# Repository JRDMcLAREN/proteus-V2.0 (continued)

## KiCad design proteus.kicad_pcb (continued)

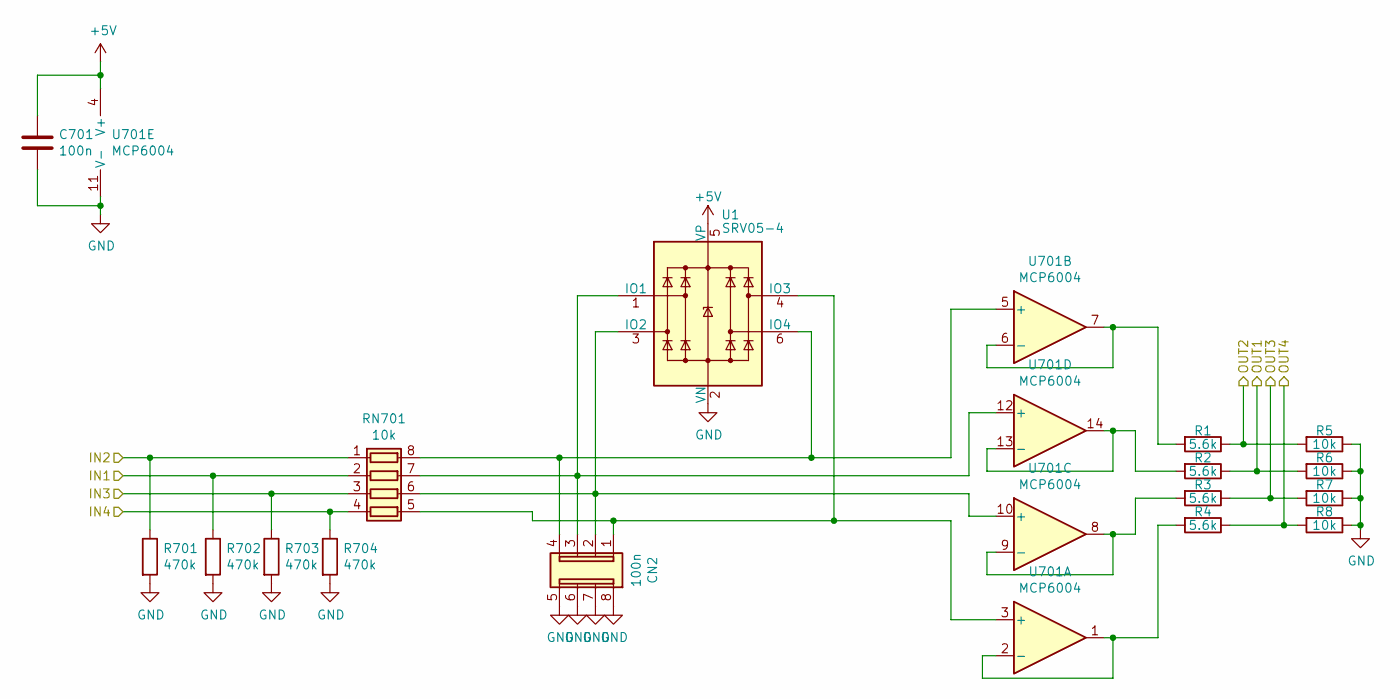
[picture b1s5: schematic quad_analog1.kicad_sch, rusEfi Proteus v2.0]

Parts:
C701: 100n; C_0603_1608Metric; LCSC C14663
CN2: 100n; R_Array_Convex_4x0603; LCSC C29718
R1, R2, R3, R4: 5.6k; R_0603_1608Metric; LCSC C25908
R5, R6, R7, R8: 10k; R_0603_1608Metric; LCSC C25744
R701, R702, R703, R704: 470k; R_0603_1608Metric; LCSC C25790
RN701: 10k; R_Array_Convex_4x0603; LCSC C29718
U1: SRV05-4; SOT-23-6; LCSC C85364
U701: MCP6004; TSSOP-14_4.4x5mm_P0.65mm; LCSC C50282

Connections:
+5V: C701.1, U1.5 (VP), U701.4 (V+); also elsewhere on the board
/AV1: R702.1, RN701.2 (R2.1); also elsewhere on the board
/AV2: R701.1, RN701.1 (R1.1); also elsewhere on the board
/AV3: R703.1, RN701.3 (R3.1); also elsewhere on the board
/AV4: R704.1, RN701.4 (R4.1); also elsewhere on the board
/mcu/AV1: R2.1, R6.2; also elsewhere on the board
/mcu/AV2: R1.1, R5.2; also elsewhere on the board
/mcu/AV3: R3.1, R7.2; also elsewhere on the board
/mcu/AV4: R4.1, R8.2; also elsewhere on the board
GND: C701.2, CN2.5 (R4.2), CN2.6 (R3.2), CN2.7 (R2.2), CN2.8 (R1.2), R5.1, R6.1, R7.1, R8.1, R701.2, R702.2, R703.2, R704.2, U1.2 (VN), U701.11 (V-); also elsewhere on the board
unnamed: CN2.1 (R1.1), RN701.5 (R4.2), U1.4 (IO3), U701.3 (+)
unnamed: CN2.2 (R2.1), RN701.6 (R3.2), U1.3 (IO2), U701.10 (+)
unnamed: CN2.3 (R3.1), RN701.7 (R2.2), U1.1 (IO1), U701.12 (+)
unnamed: CN2.4 (R4.1), RN701.8 (R1.2), U1.6 (IO4), U701.5 (+)
unnamed: R4.2, U701.1, U701.2 (-)
unnamed: R1.2, U701.6 (-), U701.7
unnamed: R3.2, U701.8, U701.9 (-)
unnamed: R2.2, U701.13 (-), U701.14

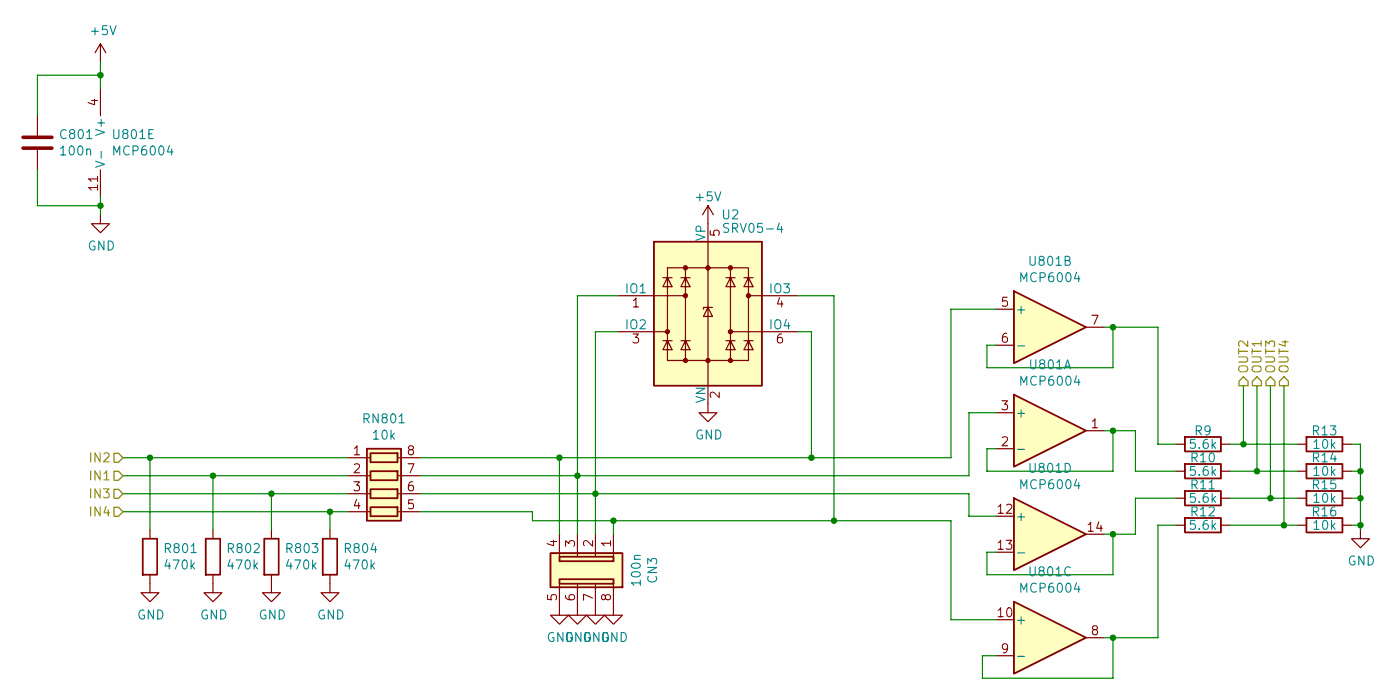
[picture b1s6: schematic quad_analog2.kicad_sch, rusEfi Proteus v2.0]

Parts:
C801: 100n; C_0603_1608Metric; LCSC C14663
CN3: 100n; R_Array_Convex_4x0603; LCSC C29718
R9, R10, R11, R12: 5.6k; R_0603_1608Metric; LCSC C25908
R13, R14, R15, R16: 10k; R_0603_1608Metric; LCSC C25744
R801, R802, R803, R804: 470k; R_0603_1608Metric; LCSC C25790
RN801: 10k; R_Array_Convex_4x0603; LCSC C29718
U2: SRV05-4; SOT-23-6; LCSC C85364
U801: MCP6004; TSSOP-14_4.4x5mm_P0.65mm; LCSC C50282

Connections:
+5V: C801.1, U2.5 (VP), U801.4 (V+); also elsewhere on the board
/AV5: R802.1, RN801.2 (R2.1); also elsewhere on the board
/AV6: R801.1, RN801.1 (R1.1); also elsewhere on the board
/AV7: R803.1, RN801.3 (R3.1); also elsewhere on the board
/AV8: R804.1, RN801.4 (R4.1); also elsewhere on the board
/mcu/AV5: R10.1, R14.2; also elsewhere on the board
/mcu/AV6: R9.1, R13.2; also elsewhere on the board
/mcu/AV7: R11.1, R15.2; also elsewhere on the board
/mcu/AV8: R12.1, R16.2; also elsewhere on the board
GND: C801.2, CN3.5 (R4.2), CN3.6 (R3.2), CN3.7 (R2.2), CN3.8 (R1.2), R13.1, R14.1, R15.1, R16.1, R801.2, R802.2, R803.2, R804.2, U2.2 (VN), U801.11 (V-); also elsewhere on the board
unnamed: CN3.1 (R1.1), RN801.5 (R4.2), U2.4 (IO3), U801.10 (+)
unnamed: CN3.2 (R2.1), RN801.6 (R3.2), U2.3 (IO2), U801.12 (+)
unnamed: CN3.3 (R3.1), RN801.7 (R2.2), U2.1 (IO1), U801.3 (+)
unnamed: CN3.4 (R4.1), RN801.8 (R1.2), U2.6 (IO4), U801.5 (+)
unnamed: R10.2, U801.1, U801.2 (-)
unnamed: R9.2, U801.6 (-), U801.7
unnamed: R12.2, U801.8, U801.9 (-)
unnamed: R11.2, U801.13 (-), U801.14

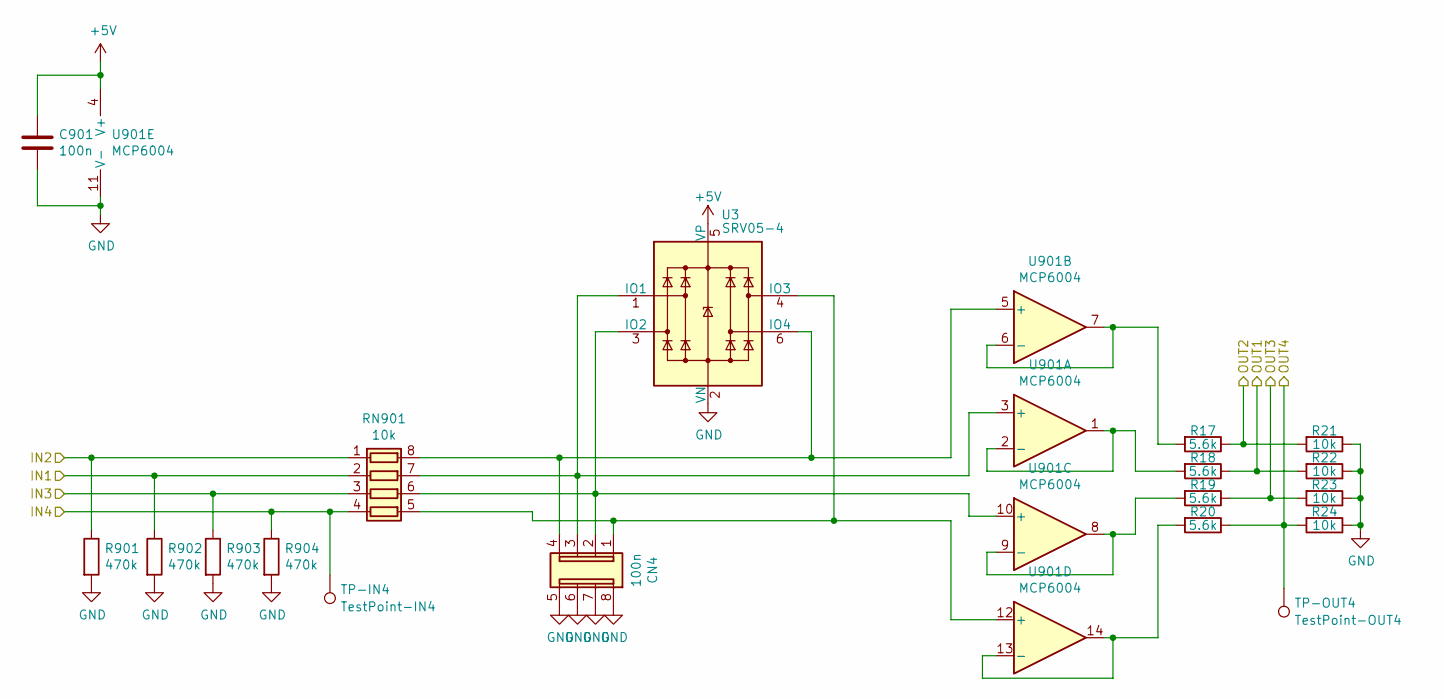
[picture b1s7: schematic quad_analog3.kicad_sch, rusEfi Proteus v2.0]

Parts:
C901: 100n; C_0603_1608Metric; LCSC C14663
CN4: 100n; R_Array_Convex_4x0603; LCSC C29718
R17, R18, R19, R20: 5.6k; R_0603_1608Metric; LCSC C25908
R21, R22, R23, R24: 10k; R_0603_1608Metric; LCSC C25744
R901, R902, R903, R904: 470k; R_0603_1608Metric; LCSC C25790
RN901: 10k; R_Array_Convex_4x0603; LCSC C29718
TP-IN4: TestPoint-IN4; TestPoint_Pad_D1.0mm
TP-OUT4: TestPoint-OUT4; TestPoint_Pad_D1.0mm
U3: SRV05-4; SOT-23-6; LCSC C85364
U901: MCP6004; TSSOP-14_4.4x5mm_P0.65mm; LCSC C50282

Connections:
+5V: C901.1, U3.5 (VP), U901.4 (V+); also elsewhere on the board
/AV9: R902.1, RN901.2 (R2.1); also elsewhere on the board
/AV10: R901.1, RN901.1 (R1.1); also elsewhere on the board
/AV11: R903.1, RN901.3 (R3.1); also elsewhere on the board
/mcu/AV9: R18.1, R22.2; also elsewhere on the board
/mcu/AV10: R17.1, R21.2; also elsewhere on the board
/mcu/AV11: R19.1, R23.2; also elsewhere on the board
/quad_analog3/IN4: R904.1, RN901.4 (R4.1), TP-IN4.1
/quad_analog3/OUT4: R20.1, R24.2, TP-OUT4.1
GND: C901.2, CN4.5 (R4.2), CN4.6 (R3.2), CN4.7 (R2.2), CN4.8 (R1.2), R21.1, R22.1, R23.1, R24.1, R901.2, R902.2, R903.2, R904.2, U3.2 (VN), U901.11 (V-); also elsewhere on the board
unnamed: CN4.1 (R1.1), RN901.5 (R4.2), U3.4 (IO3), U901.12 (+)
unnamed: CN4.2 (R2.1), RN901.6 (R3.2), U3.3 (IO2), U901.10 (+)
unnamed: CN4.3 (R3.1), RN901.7 (R2.2), U3.1 (IO1), U901.3 (+)
unnamed: CN4.4 (R4.1), RN901.8 (R1.2), U3.6 (IO4), U901.5 (+)
unnamed: R18.2, U901.1, U901.2 (-)
unnamed: R17.2, U901.6 (-), U901.7
unnamed: R19.2, U901.8, U901.9 (-)
unnamed: R20.2, U901.13 (-), U901.14

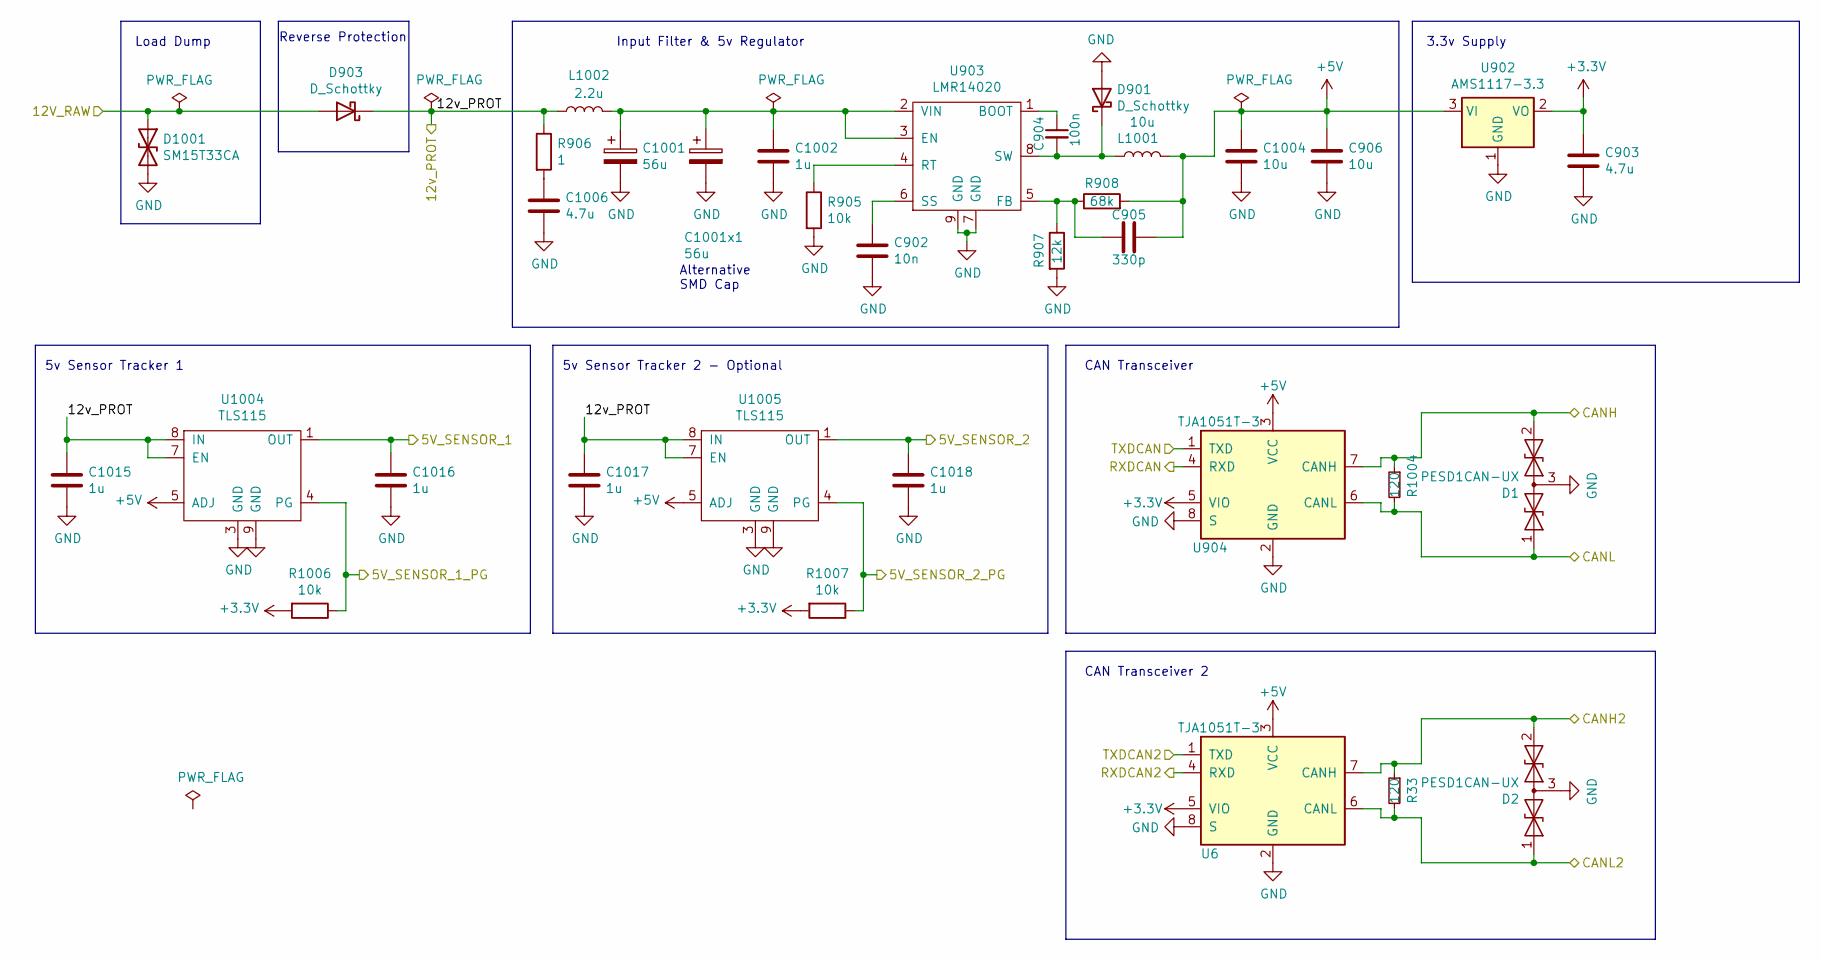
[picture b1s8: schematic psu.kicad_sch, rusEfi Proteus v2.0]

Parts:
C902: 10n; C_0603_1608Metric; LCSC C57112
C903, C1006: 4.7u; C_0603_1608Metric; LCSC C19666
C904: 100n; C_0603_1608Metric; LCSC C14663
C905: 330p; C_0603_1608Metric; LCSC C13533
C906, C1004: 10u; C_1206_3216Metric; LCSC C13585
C1001: 56u; CP_Radial_D8.0mm_P3.50mm; LCSC N/A
C1001x1: 56u; CP_Elec_6.3x9.9; LCSC N/A
C1002, C1015, C1016, C1017, C1018: 1u; C_0603_1608Metric; LCSC C15849
D1, D2: PESD1CAN-UX; SOT-323_SC-70; LCSC C152727
D901, D903: D_Schottky; D_SMA; LCSC C8678
D1001: SM15T33CA; D_SMC; LCSC C151281
L1001: 10u; MWSA0503; LCSC C408412
L1002: 2.2u; L_1210_3225Metric; LCSC C36828
R33, R1004: 120; R_0603_1608Metric; LCSC C22787
R905, R1006, R1007: 10k; R_0603_1608Metric; LCSC C25744
R906: 1; R_0603_1608Metric; LCSC C25086
R907: 12k; R_0603_1608Metric; LCSC C25752
R908: 68k; R_0603_1608Metric; LCSC C36871
U6, U904: TJA1051T-3; SOIC-8_3.9x4.9mm_P1.27mm; LCSC C38695
U902: AMS1117-3.3; SOT-223-3_TabPin2; LCSC C6186
U903: LMR14020; SOIC-8-1EP_3.9x4.9mm_P1.27mm_EP2.29x3mm; LCSC C187824
U1004, U1005: TLS115; Infineon_PG-DSO-8-43; LCSC N/A

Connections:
+3V3: C903.1, R1006.2, R1007.2, U6.5 (VIO), U902.2 (VO), U904.5 (VIO); also elsewhere on the board
+5V: C905.1, C906.1, C1004.1, L1001.2, R908.2, U6.3 (VCC), U902.3 (VI), U904.3 (VCC), U1004.5 (ADJ), U1005.5 (ADJ); also elsewhere on the board
/5V_SENSOR_1: C1016.1, U1004.1 (OUT); also elsewhere on the board
/5V_SENSOR_2: C1018.1, U1005.1 (OUT); also elsewhere on the board
/12V_PROT: C1015.1, C1017.1, D903.1 (K), L1002.1, R906.1, U1004.7 (EN), U1004.8 (IN), U1005.7 (EN), U1005.8 (IN); also elsewhere on the board
/12V_RAW: D903.2 (A), D1001.1 (A1); also elsewhere on the board
/CAN2+: D2.2 (A2), R33.1, U6.7 (CANH); also elsewhere on the board
/CAN2-: D2.1 (A1), R33.2, U6.6 (CANL); also elsewhere on the board
/CAN+: D1.2 (A2), R1004.1, U904.7 (CANH); also elsewhere on the board
/CAN-: D1.1 (A1), R1004.2, U904.6 (CANL); also elsewhere on the board
/mcu/5V_SENSOR_1_PG: R1006.1, U1004.4 (PG); also elsewhere on the board
/mcu/5V_SENSOR_2_PG: R1007.1, U1005.4 (PG); also elsewhere on the board
/mcu/CAN2_RX: U6.4 (RXD); also elsewhere on the board
/mcu/CAN2_TX: U6.1 (TXD); also elsewhere on the board
/mcu/CAN_RX: U904.4 (RXD); also elsewhere on the board
/mcu/CAN_TX: U904.1 (TXD); also elsewhere on the board
GND: C902.2, C903.2, C906.2, C1001.2, C1001x1.2, C1002.2, C1004.2, C1006.2, C1015.2, C1016.2, C1017.2, C1018.2, D1.3 (common), D2.3 (common), D901.2 (A), D1001.2 (A2), R905.2, R907.2, U6.2 (GND), U6.8 (S), U902.1 (GND), U903.7 (GND), U903.9 (GND), U904.2 (GND), U904.8 (S), U1004.3 (GND), U1004.9 (GND), U1005.3 (GND), U1005.9 (GND); also elsewhere on the board
unnamed: C1006.1, R906.2
unnamed: C904.2, D901.1 (K), L1001.1, U903.8 (SW)
unnamed: C904.1, U903.1 (BOOT)
unnamed: C1001.1, C1001x1.1, C1002.1, L1002.2, U903.2 (VIN), U903.3 (EN)
unnamed: C905.2, R907.1, R908.1, U903.5 (FB)
unnamed: R905.1, U903.4 (RT)
unnamed: C902.1, U903.6 (SS)

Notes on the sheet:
Alternative SMD Cap
3.3v Supply
CAN Transceiver 2
5v Sensor Tracker 2 - Optional
Input Filter & 5v Regulator
CAN Transceiver
Reverse Protection
Load Dump
5v Sensor Tracker 1

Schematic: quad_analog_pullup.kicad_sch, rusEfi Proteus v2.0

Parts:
C1101, C1409: 100n; C_0603_1608Metric; LCSC C14663
CN1: 100n; R_Array_Convex_4x0603; LCSC C29718
R25, R26, R27, R28: 5.6k; R_0603_1608Metric; LCSC C25908
R29, R30, R31, R32: 10k; R_0603_1608Metric; LCSC C25744
R1101, R1102, R1103, R1104: 2.7k; R_0603_1608Metric; LCSC C13167
RN1101: 10k; R_Array_Convex_4x0603; LCSC C29718
U4: SRV05-4; SOT-23-6; LCSC C85364
U1101: MCP6004; TSSOP-14_4.4x5mm_P0.65mm; LCSC C50282

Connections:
+5V: C1101.1, U4.5 (VP), U1101.4 (V+); also elsewhere on the board
/5V_SENSOR_1: C1409.2, R1101.1, R1102.1, R1103.1, R1104.1; also elsewhere on the board
/AT1: R1102.2, RN1101.2 (R2.1); also elsewhere on the board
/AT2: R1101.2, RN1101.1 (R1.1); also elsewhere on the board
/AT3: R1104.2, RN1101.4 (R4.1); also elsewhere on the board
/AT4: R1103.2, RN1101.3 (R3.1); also elsewhere on the board
/mcu/AT1: R26.1, R30.2; also elsewhere on the board
/mcu/AT2: R25.1, R29.2; also elsewhere on the board
/mcu/AT3: R28.1, R32.2; also elsewhere on the board
/mcu/AT4: R27.1, R31.2; also elsewhere on the board
GND: C1101.2, C1409.1, CN1.5 (R4.2), CN1.6 (R3.2), CN1.7 (R2.2), CN1.8 (R1.2), R29.1, R30.1, R31.1, R32.1, U4.2 (VN), U1101.11 (V-); also elsewhere on the board
unnamed: CN1.1 (R1.1), RN1101.5 (R4.2), U4.4 (IO3), U1101.12 (+)
unnamed: CN1.2 (R2.1), RN1101.6 (R3.2), U4.3 (IO2), U1101.10 (+)
unnamed: CN1.3 (R3.1), RN1101.7 (R2.2), U4.1 (IO1), U1101.3 (+)
unnamed: CN1.4 (R4.1), RN1101.8 (R1.2), U4.6 (IO4), U1101.5 (+)
unnamed: R26.2, U1101.1, U1101.2 (-)
unnamed: R25.2, U1101.6 (-), U1101.7
unnamed: R27.2, U1101.8, U1101.9 (-)
unnamed: R28.2, U1101.13 (-), U1101.14

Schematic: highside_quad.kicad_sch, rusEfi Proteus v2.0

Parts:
C1301, C1302, C1303, C1304: 10n; C_0603_1608Metric; LCSC C57112
R34, R35, R36, R37: 4.7k; R_0805_2012Metric; LCSC C17673
R1105, R1107, R1109, R1111: 10k; R_0603_1608Metric; LCSC C25744
R1106, R1108, R1110, R1112: 120; R_0603_1608Metric; LCSC C22787
RN1301: 10k; R_Array_Convex_4x0603; LCSC C29718
U1102, U1103, U1104, U1105: BTS4175SGA; SOIC-8_3.9x4.9mm_P1.27mm; LCSC C152451

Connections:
+3V3: R1105.2, R1107.2, R1109.2, R1111.2; also elsewhere on the board
/12V_MR: U1102.5 (VS), U1102.6 (VS), U1102.7 (VS), U1102.8 (VS), U1103.5 (VS), U1103.6 (VS), U1103.7 (VS), U1103.8 (VS), U1104.5 (VS), U1104.6 (VS), U1104.7 (VS), U1104.8 (VS), U1105.5 (VS), U1105.6 (VS), U1105.7 (VS), U1105.8 (VS); also elsewhere on the board
/HS1: C1301.1, R34.1, U1102.3 (OUT); also elsewhere on the board
/HS2: C1302.1, R35.1, U1103.3 (OUT); also elsewhere on the board
/HS3: C1303.1, R36.1, U1104.3 (OUT); also elsewhere on the board
/HS4: C1304.1, R37.1, U1105.3 (OUT); also elsewhere on the board
/highside_quad/IN1: RN1301.1 (R1.1); also elsewhere on the board
/highside_quad/IN2: RN1301.2 (R2.1); also elsewhere on the board
/highside_quad/IN3: RN1301.3 (R3.1); also elsewhere on the board
/highside_quad/IN4: RN1301.4 (R4.1); also elsewhere on the board
GND: C1301.2, C1302.2, C1303.2, C1304.2, R34.2, R35.2, R36.2, R37.2, R1106.2, R1108.2, R1110.2, R1112.2; also elsewhere on the board
unnamed: RN1301.8 (R1.2), U1102.2 (IN)
unnamed: RN1301.7 (R2.2), U1103.2 (IN)
unnamed: RN1301.6 (R3.2), U1104.2 (IN)
unnamed: RN1301.5 (R4.2), U1105.2 (IN)
unnamed: R1106.1, U1102.1 (GND)
unnamed: R1105.1, U1102.4 (ST)
unnamed: R1108.1, U1103.1 (GND)
unnamed: R1107.1, U1103.4 (ST)
unnamed: R1110.1, U1104.1 (GND)
unnamed: R1109.1, U1104.4 (ST)
unnamed: R1112.1, U1105.1 (GND)
unnamed: R1111.1, U1105.4 (ST)

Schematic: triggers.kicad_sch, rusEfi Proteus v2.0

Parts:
C1204, C1205, C1207, C1208, C1209, C1210, C1401, C1402, C1403, C1404, C1405, C1406, C1407, C1408: 1n; C_0603_1608Metric; LCSC C1588
C1211: 100n; C_0603_1608Metric; LCSC C14663
C1212: 1u; C_0603_1608Metric; LCSC C15849
JP1201: Jumper_3_Bridged12; SolderJumper-3_P1.3mm_Bridged12_RoundedPad1.0x1.5mm; LCSC N/A
R1201, R1202, R1203, R1204, R1401, R1402, R1403, R1404, R1405, R1406, R1407, R1408: 2.7k; R_0603_1608Metric; LCSC C13167
R1205, R1206, R1208, R1209, R1210, R1211, R1213, R1214, R1215, R1216: 4.7k; R_0805_2012Metric; LCSC C17673
R1207, R1212: DNP; R_0805_2012Metric; LCSC DNP
R1217, R1218: 1k; R_0603_1608Metric; LCSC C11702
R1219, R1220: DNP; R_0805_2012Metric_Pad1.15x1.40mm_HandSolder; LCSC DNP
U1106, U1107: SRV05-4; SOT-23-6
U1202, U1207, U1208: SN74LVC2G17DB; SOT-23-6; LCSC C10429
U1203, U1204: MAX9924; MSOP-10_3x3mm_P0.5mm; LCSC N/A

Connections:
+3V3: R1215.1, R1216.1; also elsewhere on the board
+5V: C1211.1, JP1201.1 (A), R1217.1, U1106.5 (VP), U1107.5 (VP), U1202.5 (VCC), U1203.9 (INT_THRS), U1203.10 (VCC), U1204.10 (VCC), U1207.5 (VCC), U1208.5 (VCC); also elsewhere on the board
/5V_SENSOR_1: R1201.1, R1203.1, R1401.1, R1403.1, R1405.1, R1407.1; also elsewhere on the board
/DIGITAL_1: C1401.1, R1401.2, R1402.2; also elsewhere on the board
/DIGITAL_2: C1403.1, R1403.2, R1404.2; also elsewhere on the board
/DIGITAL_3: C1405.1, R1405.2, R1406.2; also elsewhere on the board
/DIGITAL_4: C1407.1, R1407.2, R1408.2; also elsewhere on the board
/DIGITAL_5: C1204.1, R1201.2, R1202.2; also elsewhere on the board
/DIGITAL_6: C1207.1, R1203.2, R1204.2; also elsewhere on the board
/VR1+: R1205.2; also elsewhere on the board
/VR1-: R1208.2; also elsewhere on the board
/VR2+: R1210.2; also elsewhere on the board
/VR2-: R1213.2; also elsewhere on the board
/mcu/DIGITAL1: U1202.6; also elsewhere on the board
/mcu/DIGITAL2: U1207.6; also elsewhere on the board
/mcu/DIGITAL3: U1207.4; also elsewhere on the board
/mcu/DIGITAL4: U1208.6; also elsewhere on the board
/mcu/DIGITAL5: U1202.4; also elsewhere on the board
/mcu/DIGITAL6: U1208.4; also elsewhere on the board
/mcu/VR_1: R1215.2, R1220.1, U1203.7 (COUT); also elsewhere on the board
/mcu/VR_2: R1216.2, U1204.7 (COUT); also elsewhere on the board
GND: C1204.2, C1205.2, C1207.2, C1208.2, C1211.2, C1212.2, C1401.2, C1402.2, C1403.2, C1404.2, C1405.2, C1406.2, C1407.2, C1408.2, JP1201.3 (B), R1218.1, U1106.2 (VN), U1107.2 (VN), U1202.2 (GND), U1203.5 (GND), U1204.4 (BIAS), U1204.5 (GND), U1204.6 (ZERO_EN), U1204.9 (INT_THRS), U1207.2 (GND), U1208.2 (GND); also elsewhere on the board
unnamed: JP1201.2 (C), U1203.6 (ZERO_EN)
unnamed: R1205.1, R1206.2
unnamed: R1208.1, R1209.2
unnamed: R1210.1, R1211.2
unnamed: R1213.1, R1214.2
unnamed: C1205.1, R1202.1, U1106.1 (IO1), U1202.3
unnamed: C1402.1, R1402.1, U1106.3 (IO2), U1202.1
unnamed: C1404.1, R1404.1, U1106.4 (IO3), U1207.1
unnamed: C1406.1, R1406.1, U1106.6 (IO4), U1207.3
unnamed: C1408.1, R1408.1, U1107.1 (IO1), U1107.6 (IO4), U1208.1
unnamed: C1208.1, R1204.1, U1107.3 (IO2), U1107.4 (IO3), U1208.3
unnamed: C1212.1, R1217.2, R1218.2, R1219.2, U1203.4 (BIAS)
unnamed: R1219.1, R1220.2, U1203.8 (EXT)
unnamed: C1209.2, R1207.1, R1209.1, U1203.1 (IN+)
unnamed: C1209.1, R1206.1, R1207.2, U1203.2 (IN-)
unnamed: C1210.2, R1212.1, R1214.1, U1204.1 (IN+)
unnamed: C1210.1, R1211.1, R1212.2, U1204.2 (IN-)

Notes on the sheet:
Crazy pin routing is to make PCB layout simpler
Optional setting in Mode C for no adaptive threshold timeout - See MAX9924 Datasheet Components as specified put chip in mode A1. Flip jumper and install R1219+R2020 for mode C.
Yes, we know that the polarity is flipped going in to the VR interface chips. While originally on accident, it’s no big deal since they invert anyway: When VR+ transitions to a higher voltage than VR-, VR_OUT will output a rising edge. See issue https://github.com/mck1117/proteus/issues/57 for more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

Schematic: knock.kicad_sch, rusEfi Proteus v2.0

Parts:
C18, C19: 10u; C_1206_3216Metric; LCSC C13585
C21, C22: 680p; C_0603_1608Metric; LCSC C1630
C23, C24: 330p; C_0603_1608Metric; LCSC C13533
C25, C26: 47p; C_0603_1608Metric; LCSC C1567
C1901, C1902: 3.3n; C_0805_2012Metric; LCSC C53175
C1903: 10n; C_0603_1608Metric; LCSC C57112
J3: AudioJack3; Jack_3.5mm_CUI_SJ1-3533NG_Horizontal; LCSC N/A
JP1, JP2: Jumper_NO_Small; SolderJumper-2_P1.3mm_Open_TrianglePad1.0x1.5mm; LCSC N/A
R38, R40, R46, R47: 33k; R_0603_1608Metric; LCSC C25779
R42, R43: 12k; R_0603_1608Metric; LCSC C25752
R44, R45, R1901, R1902: 100k; R_0603_1608Metric; LCSC C25741
R1903, R1904: 470k; R_0603_1608Metric; LCSC C25790
U5: MCP6004; TSSOP-14_4.4x5mm_P0.65mm; LCSC C50282
U7: MCP6002-xSN; SOIC-8_3.9x4.9mm_P1.27mm; LCSC C7377

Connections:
+3V3: R40.2, U5.4 (V+); also elsewhere on the board
+5V: U7.8 (V+); also elsewhere on the board
/KNOCK_1: C1901.2, JP1.1; also elsewhere on the board
/KNOCK_2: C1902.2, JP2.1; also elsewhere on the board
/knock/FILTERED_1: C23.2, U5.6 (-), U5.7, U7.3 (+); also elsewhere on the board
/knock/FILTERED_2: C24.2, U5.8, U5.9 (-), U7.5 (+); also elsewhere on the board
/knock/V_mid: C1903.2, R38.1, R40.1, U5.3 (+), U5.12 (+)
GND: C21.1, C22.1, C25.1, C26.1, C1903.1, J3.S, R38.2, U5.11 (V-), U7.4 (V-); also elsewhere on the board
unnamed: C18.1, J3.R
unnamed: C19.1, J3.T
unnamed: C21.2, R42.1, R44.2
unnamed: C22.2, R43.1, R45.2
unnamed: C23.1, R44.1, R46.2
unnamed: C24.1, R45.1, R47.2
unnamed: C1901.1, JP1.2, R1901.2
unnamed: C1902.1, JP2.2, R1902.2
unnamed: R42.2, R1903.1, U5.1
unnamed: R43.2, R1904.1, U5.14
unnamed: R1901.1, R1903.2, U5.2 (-)
unnamed: C25.2, R46.1, U5.5 (+)
unnamed: C26.2, R47.1, U5.10 (+)
unnamed: R1902.1, R1904.2, U5.13 (-)
unnamed: C19.2, U7.1, U7.2 (-)
unnamed: C18.2, U7.6 (-), U7.7

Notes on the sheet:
Line Out
Short jumper if DC is interesting

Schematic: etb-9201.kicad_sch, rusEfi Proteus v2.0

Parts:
C28, C29: 10n; C_0603_1608Metric; LCSC C57112
C1201: 10u; C_1206_3216Metric; LCSC C13585
R48: 10k; R_0603_1608Metric; LCSC C25744
U11: TLE9201SG; Infineon_PG-DSO-12-9; LCSC C112633

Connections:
+3V3: R48.2, U11.2 (VSO); also elsewhere on the board
/12V_MR: C1201.2, U11.4 (VS); also elsewhere on the board
/ETB2+: C28.2, U11.5 (OUT1); also elsewhere on the board
/ETB2-: C29.1, U11.7 (OUT2); also elsewhere on the board
/etb-2/DIR: U11.1 (DIR); also elsewhere on the board
/etb-2/DIS: R48.1, U11.11 (DIS); also elsewhere on the board
/etb-2/PWM: U11.12 (PWM); also elsewhere on the board
GND: C28.1, C29.2, C1201.1, U11.6 (GND), U11.13 (GND); also elsewhere on the board

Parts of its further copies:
C27: 10u; C_1206_3216Metric; LCSC C13585
C1202, C1203: 10n; C_0603_1608Metric; LCSC C57112
R1001: 10k; R_0603_1608Metric; LCSC C25744
U10: TLE9201SG; Infineon_PG-DSO-12-9; LCSC C112633

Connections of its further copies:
+3V3: R1001.2, U10.2 (VSO); also elsewhere on the board
/12V_MR: C27.2, U10.4 (VS); also elsewhere on the board
/ETB1+: C1202.2, U10.5 (OUT1); also elsewhere on the board
/ETB1-: C1203.1, U10.7 (OUT2); also elsewhere on the board
/etb-1/DIR: U10.1 (DIR); also elsewhere on the board
/etb-1/DIS: R1001.1, U10.11 (DIS); also elsewhere on the board
/etb-1/PWM: U10.12 (PWM); also elsewhere on the board
GND: C27.1, C1202.1, C1203.2, U10.6 (GND), U10.13 (GND); also elsewhere on the board

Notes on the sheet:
IFX9201 also acceptable

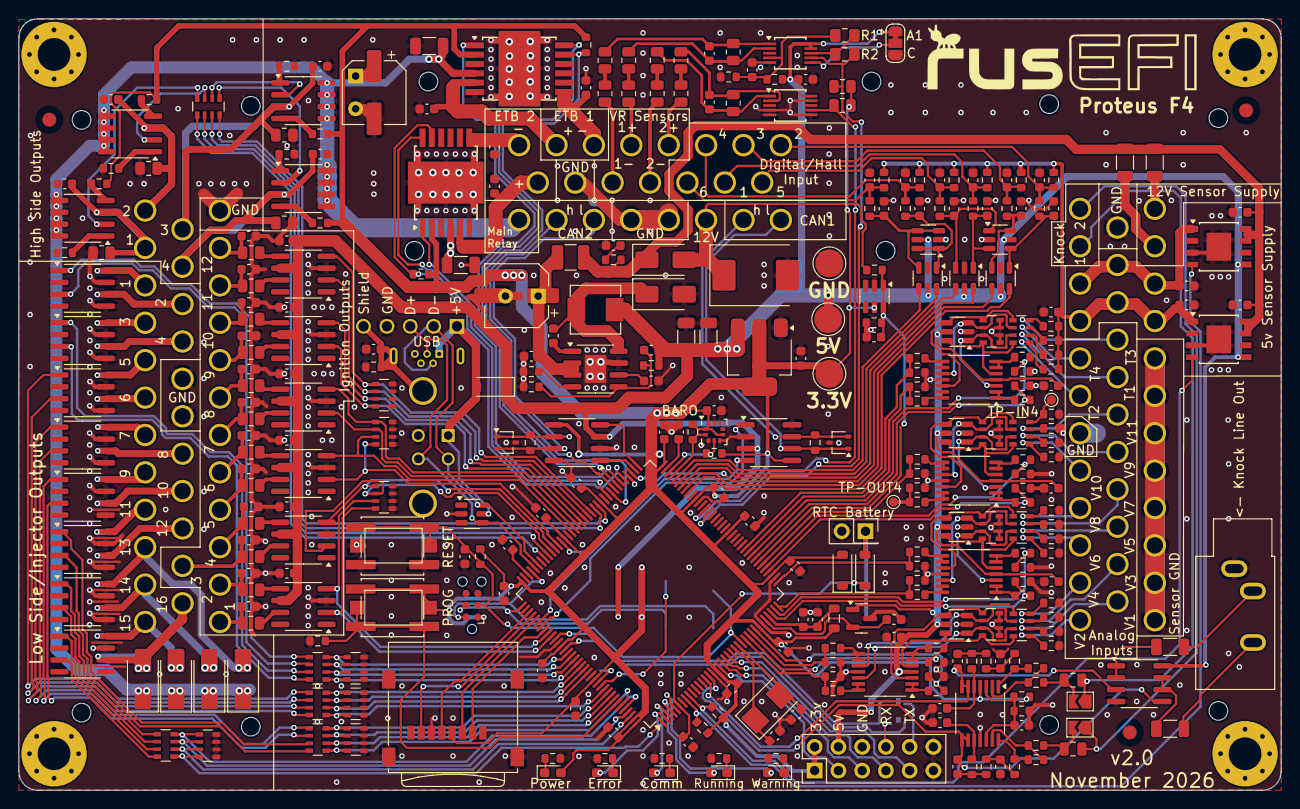
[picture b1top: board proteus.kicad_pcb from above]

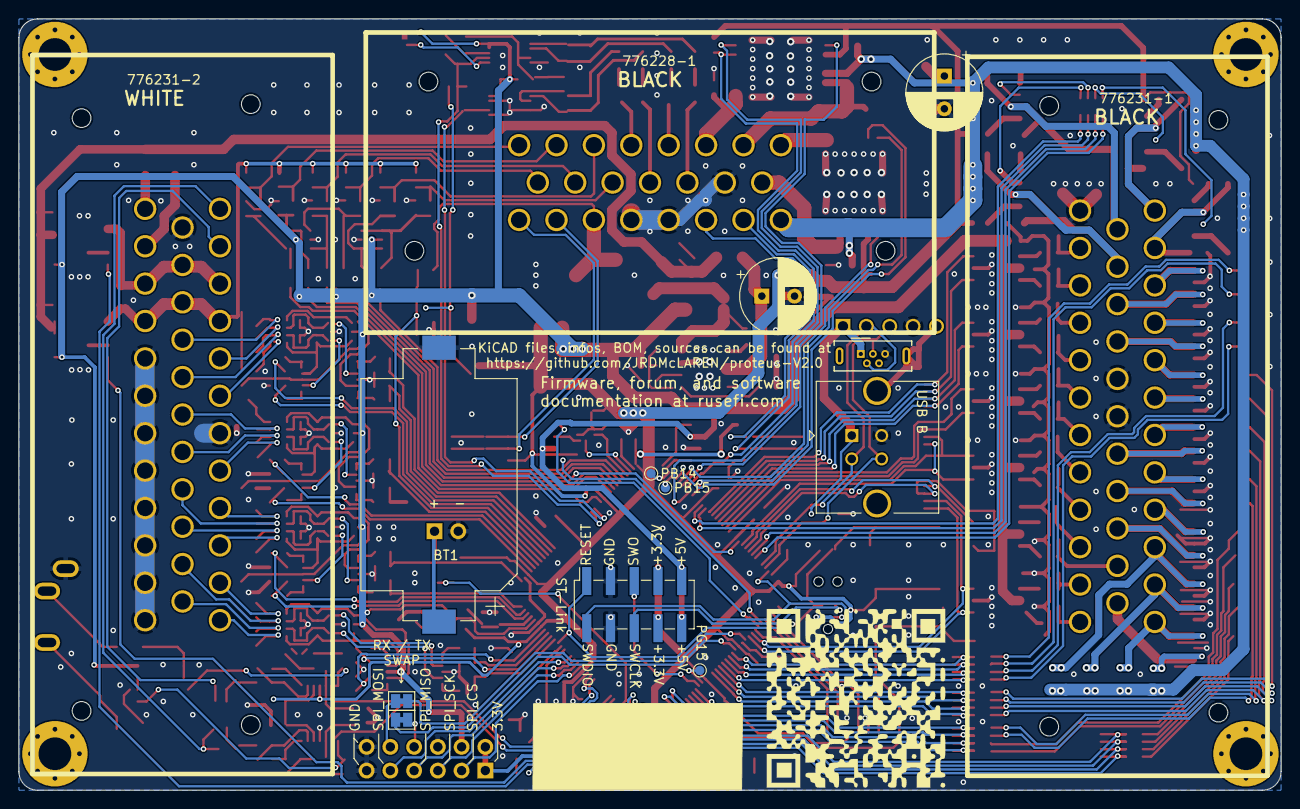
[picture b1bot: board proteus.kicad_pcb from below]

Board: 2 copper layers, 135.0 x 82.5 mm, 360 parts (14 on the bottom side), 305 nets.

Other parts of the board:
LOGO: LOGO; mre_logo
M3, M3#2, M3#3, M3#4: MountingHole_3.5mm_Pad_Via
